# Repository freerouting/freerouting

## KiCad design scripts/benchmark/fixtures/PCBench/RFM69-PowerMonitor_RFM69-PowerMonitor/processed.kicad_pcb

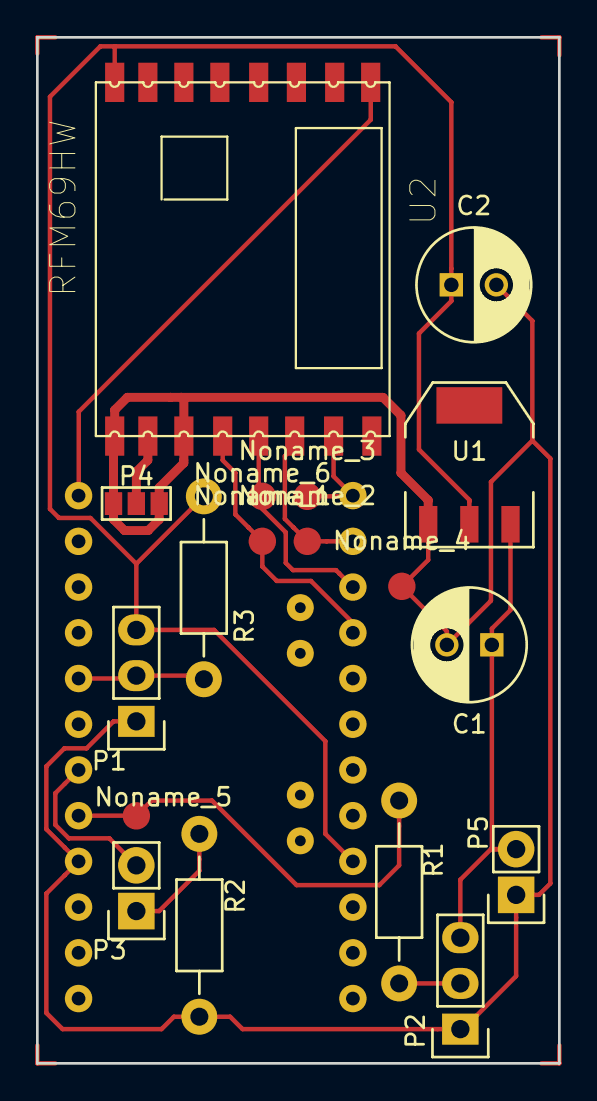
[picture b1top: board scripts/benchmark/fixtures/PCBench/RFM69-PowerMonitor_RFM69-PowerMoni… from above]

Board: 2 copper layers, 29.0 x 57.0 mm, 19 parts (1 on the bottom side), 14 nets.

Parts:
C1: 10uF; C_Radial_D6.3_L11.2_P2.5
C2: 100uF; C_Radial_D6.3_L11.2_P2.5
Noname_1, Noname_2, Noname_3, Noname_4, Noname_5, Noname_6: Measurement_Point_Round-SMD-Pad_Small
P1: 1WIRE; Pin_Header_Straight_1x03
P2: CONN_PIR; Pin_Header_Straight_1x03
P3: MTR; Pin_Header_Straight_1x02
P4: ANT; GS3
P5: CONN_PWR; Pin_Header_Straight_1x02
R1, R2: 470; Resistor_Horizontal_RM10mm
R3: 2.2k; Resistor_Horizontal_RM10mm
U1: AP1117D33; SOT-223
U2: RFM69HW; RFM
uP1: ARDUPROMINI-6; ArduProMini-6

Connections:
+5V: C1.1, P2.3, P5.2, U1.3
GND: C1.2, C2.2, Noname_4.1, P1.1, P2.1, P4.1, P4.3, P5.1, R2.1, U1.1, U2.GNDA, U2.GNDB, uP1.10
unnamed: C2.1, P1.3, R3.1, U1.2, U2.VCC, uP1.22
unnamed: P1.2, R3.2, uP1.14
unnamed: P2.2, R1.2
unnamed: P3.1, R2.2
unnamed: P3.2, uP1.12
unnamed: P4.2, U2.ANT
unnamed: Noname_5.1, R1.1, uP1.11
unnamed: Noname_6.1, U2.MISO, uP1.28
unnamed: Noname_2.1, U2.MOSI, uP1.29
unnamed: Noname_3.1, U2.NSS, uP1.30
unnamed: U2.RESE, uP1.18
unnamed: Noname_1.1, U2.SCK, uP1.27

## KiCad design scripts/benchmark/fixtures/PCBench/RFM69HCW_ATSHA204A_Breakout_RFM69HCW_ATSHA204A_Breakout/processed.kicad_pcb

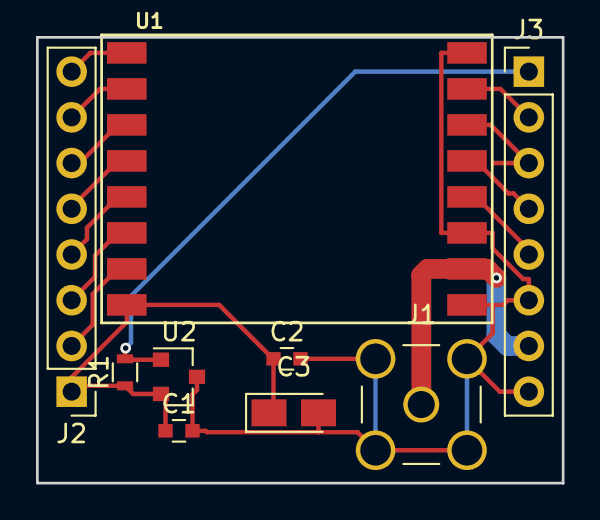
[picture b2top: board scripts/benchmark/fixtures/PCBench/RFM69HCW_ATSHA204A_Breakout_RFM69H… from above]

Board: 2 copper layers, 29.2 x 24.8 mm, 9 parts (0 on the bottom side), 15 nets.

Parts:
C1, C2: C; C_0603
C3: CP; CP_Tantalum_Case-S_EIA-3216-12_Reflow
J1: CONN_COAXIAL; SMA_THT_Jack_Straight
J2, J3: CONN_01X08; Pin_Header_Straight_1x08_Pitch2.54mm
R1: R; R_0603
U1: RFM69HW; RFM69HW_SMD
U2: ATSHA204A; SOT-23

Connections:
+3V3: C1.1, C2.1, C3.1, J2.1, R1.1, U1.8, U2.2
/ANA: J1.1, J3.7, U1.10
/ATSHA: J3.1, R1.2, U2.1
/DIO0: J2.7, U1.2
/DIO1: J2.6, U1.3
/DIO2: J2.5, U1.4
/DIO3: J2.4, U1.5
/DIO4: J2.3, U1.6
/DIO5: J2.2, U1.7
/MISO: J3.4, U1.13
/MOSI: J3.3, U1.14
/NSS: J3.2, U1.15
/RST: J2.8, U1.1
/SCK: J3.5, U1.12
GND: C1.2, C2.2, C3.2, J1.2, J3.6, J3.8, U1.9, U1.11, U1.16, U2.3

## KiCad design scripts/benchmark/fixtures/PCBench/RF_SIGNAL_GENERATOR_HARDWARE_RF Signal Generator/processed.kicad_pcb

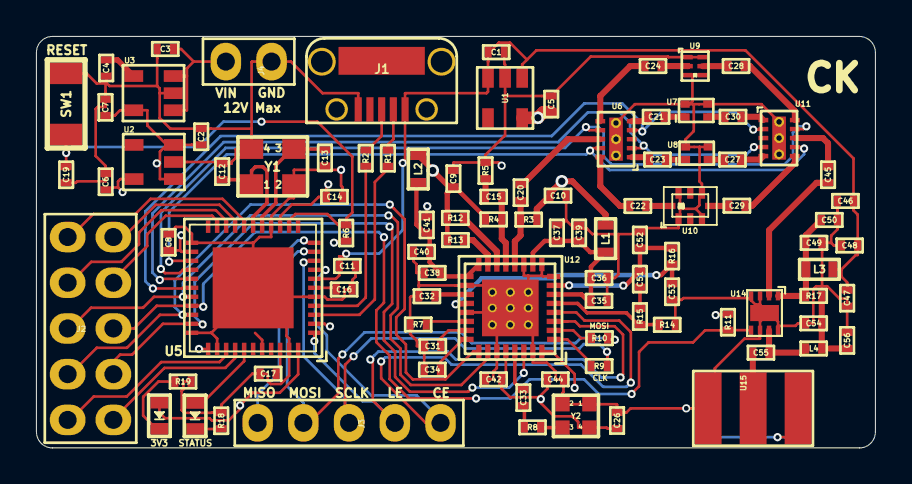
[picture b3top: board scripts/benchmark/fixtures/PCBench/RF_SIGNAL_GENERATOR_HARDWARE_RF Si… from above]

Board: 4 copper layers, 46.6 x 22.9 mm, 98 parts (0 on the bottom side), 80 nets.

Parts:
3V3: Led_Diode; Diode_0603
C1, C2, C3, C4, C5, C6, C7: 2.2uF; SMD_0402
C8, C14, C17, C19, C35, C36, C38, C40, C42, C44, C48, C50, C51: 100nF; SMD_0402
C9, C10, C37, C39, C41: 100pF; SMD_0402
C11, C16, C31, C32, C34: 1uF; SMD_0402
C12, C13: 15pF; SMD_0402
C15, C20, C45, C55: 1nF; SMD_0402
C21, C22, C23, C24, C27, C28, C29, C30, C54: 10pF; SMD_0402
C26, C33, C56: 10nF; SMD_0402
C46, C47: DNP; SMD_0402
C49: 10uF; SMD_0402
C52: 12nF; SMD_0402
C53: 820pF; SMD_0402
J1: USB_MicroB; USB_MicroB_TH
J2: Connector_02x05; PinHeader_2x5_P2.54mm
J3: Connector_01x05; PinHeader_1x5_P2.54mm
J4: Connector_01x02; PinHeader_1x2_P2.54mm
L1, L2, L3: BLM18PG181SN1D; SMD_0603
L4: LQW15AN9N9J80D; SMD_0402
R1, R2: 22; SMD_0402
R3, R4, R5: 49.9; SMD_0402
R6: 10K; SMD_0402
R7: 5.11K; SMD_0402
R8, R9, R10, R12, R13: 0; SMD_0402
R11: 100; SMD_0402
R14: 90.9; SMD_0402
R15: 30.1; SMD_0402
R16: 240; SMD_0402
R17: 1.8; SMD_0402
R18, R19: 1K; SMD_0402
STATUS: Led_Diode; Diode_0603
SW1: RESET_BUTTON; Button_B3U_1000P
U1, U2: LP5907; SOT23_5
U3: MIC5219; SOT23_5
U5: ATMEGA32U4; QFN44_7x7mm_P0.5mm_1EXP_4.5x4.5mm
U6, U11: SKY13322_375LF; MLPD_10
U7: LPF_LP0603A0902ANTR
U8: LPF_LP0603A1842ANTR
U9: LPF_3550LP14A300T
U10: LPF_5515LP15A730E
U12: MAX2871; QFN32_5x5mm_P0.5mm_1EXP_3.1x3.1mm
U14: TRF37A75; WSON8_2x2mm_P0.5mm_1EXP_0.9x1.6mm
U15: SMA_Connector
Y1: 8MHz; Crystal_3.2x2.5mm
Y2: ASTX-13-D-19.200MHz-I05-T; Crystal_2x1.6mm

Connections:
+3V3: 3V3.2, C6.1, C8.1, C14.1, C26.1, C42.2, C44.2, R6.1, R11.1, U2.5, U5.14, U5.24, U5.34, U5.44, U12.28, U12.32, Y2.4
+5V: C1.1, C2.1, C7.1, C11.1, C46.1, C47.1, C48.1, J1.1, L3.1, U1.1, U1.3, U2.1, U2.3, U3.5, U5.2, U5.7
+VBattery: C3.1, J4.2, U3.1, U3.3
/3.3V_RF: C5.1, C9.2, C10.2, L1.1, L2.1, R3.1, R4.1, R12.1, R13.1, U1.5
/D+: R2.2, U5.4
/D-: R1.2, U5.3
/RST: C19.2, R6.2, SW1.1, U5.13
ADC6: J2.10, U5.37
ADC7: J2.9, U5.36
AMP_PWDN: J2.6, R11.2, U5.30, U14.5
GND: C1.2, C2.2, C3.2, C4.2, C5.2, C6.2, C7.2, C8.2, C9.1, C10.1, C11.2, C12.2, C13.2, C14.2, C16.2, C17.2, C19.1, C26.2, C31.1, C32.1, C34.1, C35.1, C36.1, C37.1, C38.1, C39.1, C40.1, C41.1, C42.1, C44.1, C46.2, C47.2, C48.2, C49.2, C50.2, C52.1, C53.1, C54.2, C56.2, J1.5, J4.1, R5.1, R7.2, R14.1, R18.2, R19.2, SW1.2, U1.2, U2.2, U3.2, U5.5, U5.15, U5.23, U5.33, U5.35, U5.43, U5.45, U6.11, U7.3, U7.4, U8.3, U8.4, U9.1, U9.3, U9.4, U9.6, U10.1, U10.3, U10.5, U10.7, U11.11, U12.8, U12.9, U12.11, U12.18, U12.21, U12.27, U12.31, U12.33, U14.3, U14.4, U14.6, U14.8, U14.9, U15.2, U15.3, U15.4, U15.5, Y1.2, Y1.4, Y2.1, Y2.2
MAX2871_CE: J3.1, U5.8, U12.4
MAX2871_LD: J2.7, U5.31, U12.25
MAX2871_LE: J3.2, U5.1, U12.3
MAX2871_MUX: J2.8, U5.32, U12.30
unnamed: C4.1, U3.4
unnamed: C12.1, U5.17, Y1.1
unnamed: C13.1, U5.16, Y1.3
unnamed: C15.2, R5.2
unnamed: C16.1, U5.6
unnamed: C17.1, U5.42
unnamed: C20.2, U6.8
unnamed: C21.1, U7.1
unnamed: C21.2, U6.5
unnamed: C22.1, U10.8
unnamed: C22.2, U6.10
unnamed: C23.1, U8.1
unnamed: C23.2, U6.1
unnamed: C24.1, U9.2
unnamed: C24.2, U6.6
unnamed: C27.1, U11.5
unnamed: C27.2, U8.2
unnamed: C28.1, U11.10
unnamed: C28.2, U9.5
unnamed: C29.1, U11.6
unnamed: C29.2, U10.4
unnamed: C30.1, U11.1
unnamed: C30.2, U7.2
unnamed: C31.2, U12.23
unnamed: C32.2, U12.19
unnamed: C33.1, U12.29
unnamed: C33.2, R8.2
unnamed: C34.2, U12.24
unnamed: C35.2, C36.2, C37.2, C39.2, L1.2, U12.6, U12.10
unnamed: C38.2, C40.2, C41.2, L2.2, U12.16, U12.17
unnamed: C45.1, U14.2
unnamed: C45.2, U11.8
unnamed: C49.1, C50.1, L3.2, R17.1, U14.1
unnamed: C51.1, C52.2, R16.1, U12.7
unnamed: C51.2, R15.1
unnamed: C53.2, R16.2, U12.20
unnamed: C54.1, C56.1, L4.1, R17.2
unnamed: C55.1, L4.2, U14.7
unnamed: C55.2, U15.1
unnamed: R18.1, STATUS.1
unnamed: 3V3.1, R19.1
unnamed: J1.2, R1.1
unnamed: J1.3, R2.1
unnamed: R7.1, U12.22
unnamed: R9.2, U12.1
unnamed: R10.2, U12.2
unnamed: R12.2, U12.14
unnamed: R13.2, U12.15
unnamed: R14.2, R15.2, U12.5
REF_IN: R8.1, Y2.3
RFOUTA_N: C15.1, R4.2, U12.13
RFOUTA_P: C20.1, R3.2, U12.12
RFOUT_EN: J2.5, U5.29, U12.26
RX: J2.3, U5.20
SCL: J2.1, U5.18
SDA: J2.2, U5.19
SPI_CLK: J3.3, R9.1, U5.9
SPI_MISO: J3.5, U5.11
SPI_MOSI: J3.4, R10.1, U5.10
STATUS_LED: STATUS.2, U5.38
SWITCH_V1: U5.25, U6.9, U11.7
SWITCH_V2: U5.26, U6.7, U11.9
SWITCH_V3: U5.27, U6.2, U11.4
SWITCH_V4: U5.28, U6.4, U11.2
TX: J2.4, U5.21
